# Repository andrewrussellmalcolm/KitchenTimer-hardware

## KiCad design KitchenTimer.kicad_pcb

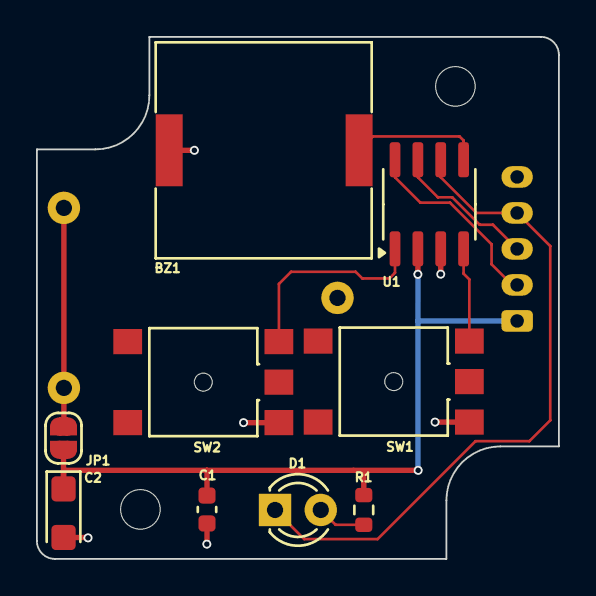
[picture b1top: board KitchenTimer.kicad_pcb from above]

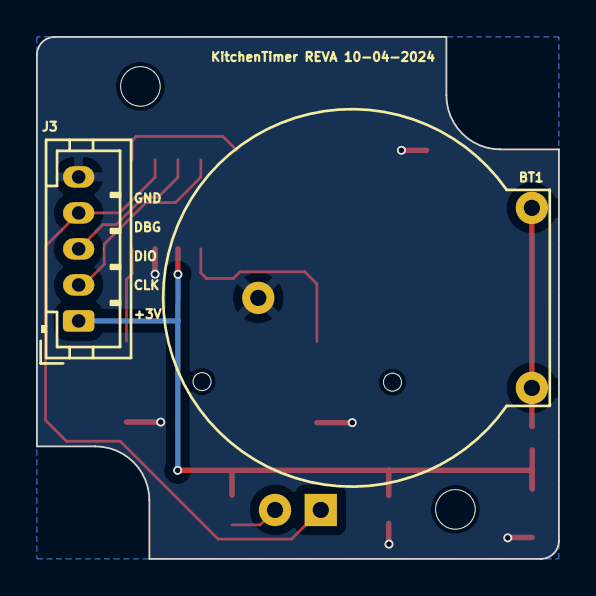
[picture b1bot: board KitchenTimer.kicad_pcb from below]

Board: 2 copper layers, 29.0 x 29.0 mm, 15 parts (2 on the bottom side), 10 nets.

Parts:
BT1: Battery_Cell; Trupower-CR2032-PCB-mount
BZ1: Buzzer; Buzzer_Murata_PKLCS1212E4001-R1
C1: 100n; C_0603_1608Metric
C2: 10u; CP_EIA-3216-10_Kemet-I
D1: LED_Filled; LED_D3.0mm
H1, H2: MountingHole; MountingHole_2.2mm_M2
H3, H4: MountingHole; LocationHole_1mm
J3: Conn_01x05; JST_PH_B5B-PH-K_1x05_P2.00mm_Vertical
JP1: Jumper_2_Bridged; SolderJumper-2_P1.3mm_Open_RoundedPad1.0x1.5mm
R1: 4K7; R_0603_1608Metric
SW1, SW2: SW_Push; SW_TS06-667-50-BK-100-G-SMT-TR
U1: STM32G041J6Mx; SOIC-8_3.9x4.9mm_P1.27mm

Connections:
+3V0: C1.2, C2.1, J3.1, JP1.2 (B), R1.2, U1.2 (VDD)
+BATT: BT1.1 (+), JP1.1 (A)
GND: BT1.2 (-), BZ1.2 (+), C1.1, C2.2, J3.5, SW1.1, SW2.1, U1.3 (VSS)
unnamed: BZ1.1 (-), U1.5 (PB0/PB1/PA8/PA11/PA9)
unnamed: D1.2 (A), R1.1
unnamed: D1.1 (K), J3.4, U1.6 (PA12/PA10)
unnamed: SW2.2, U1.1 (PC14/PB7/PB8/PB9)
unnamed: SW1.2, U1.4 (PF2/PA0/PA1/PA2)
SWCLK: J3.2, U1.8 (PA14/PA15/PB5/PB6)
SWDIO: J3.3, U1.7 (PA13)

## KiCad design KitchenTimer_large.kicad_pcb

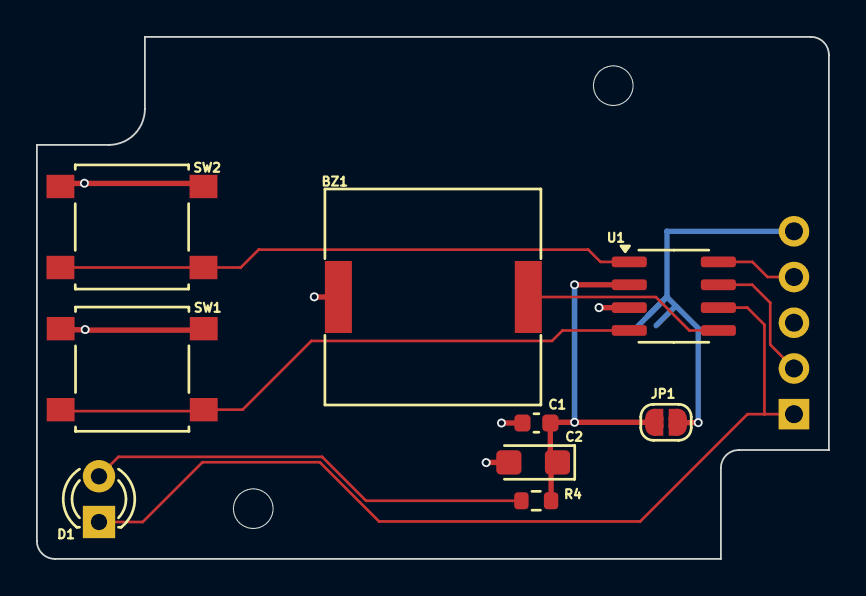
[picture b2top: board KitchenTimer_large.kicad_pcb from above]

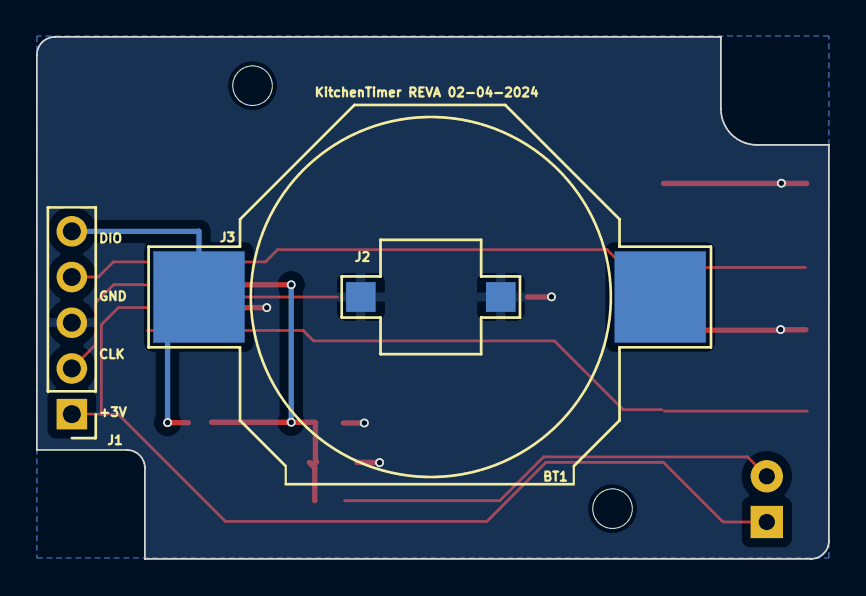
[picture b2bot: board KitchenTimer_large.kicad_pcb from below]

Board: 2 copper layers, 44.0 x 29.0 mm, 15 parts (4 on the bottom side), 10 nets.

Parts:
BT1: CR2032; CR2032_battery
BZ1: Buzzer; Buzzer_Murata_PKLCS1212E4001-R1
C1: 100n; C_0603_1608Metric
C2: 10u; CP_EIA-3216-10_Kemet-I
D1: LED_Filled; LED_D3.0mm
H1, H2: MountingHole; MountingHole_2.2mm_M2
J1: Conn_01x05; PinHeader_1x05_P2.54mm_Vertical
J2: 2991 cell negative; SM_BATTERY_2991_(KEYSTONE)_1
J3: 3002 cell positive; SM_BATTERY_3002_(KEYSTONE)_1
JP1: Jumper_2_Bridged; SolderJumper-2_P1.3mm_Open_RoundedPad1.0x1.5mm
R4: 4K7; R_0603_1608Metric
SW1, SW2: SW_Push; SW_SPST_B3S-1000
U1: STM32G041J6Mx; SOIC-8_3.9x4.9mm_P1.27mm

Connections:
+3V0: C1.2, C2.1, JP1.2 (B), R4.2, U1.2 (VDD)
+BATT: J1.5, J3.2, JP1.1 (A)
GND: BZ1.2 (+), C1.1, C2.2, J1.3, J2.1, J2.2, SW1.1, SW2.1, U1.3 (VSS)
unnamed: BZ1.1 (-), U1.5 (PB0/PB1/PA8/PA11/PA9)
unnamed: D1.2 (A), R4.1
unnamed: D1.1 (K), J1.1, U1.6 (PA12/PA10)
unnamed: SW2.2, U1.1 (PC14/PB7/PB8/PB9)
unnamed: SW1.2, U1.4 (PF2/PA0/PA1/PA2)
SWCLK: J1.4, U1.8 (PA14/PA15/PB5/PB6)
SWDIO: J1.2, U1.7 (PA13)
